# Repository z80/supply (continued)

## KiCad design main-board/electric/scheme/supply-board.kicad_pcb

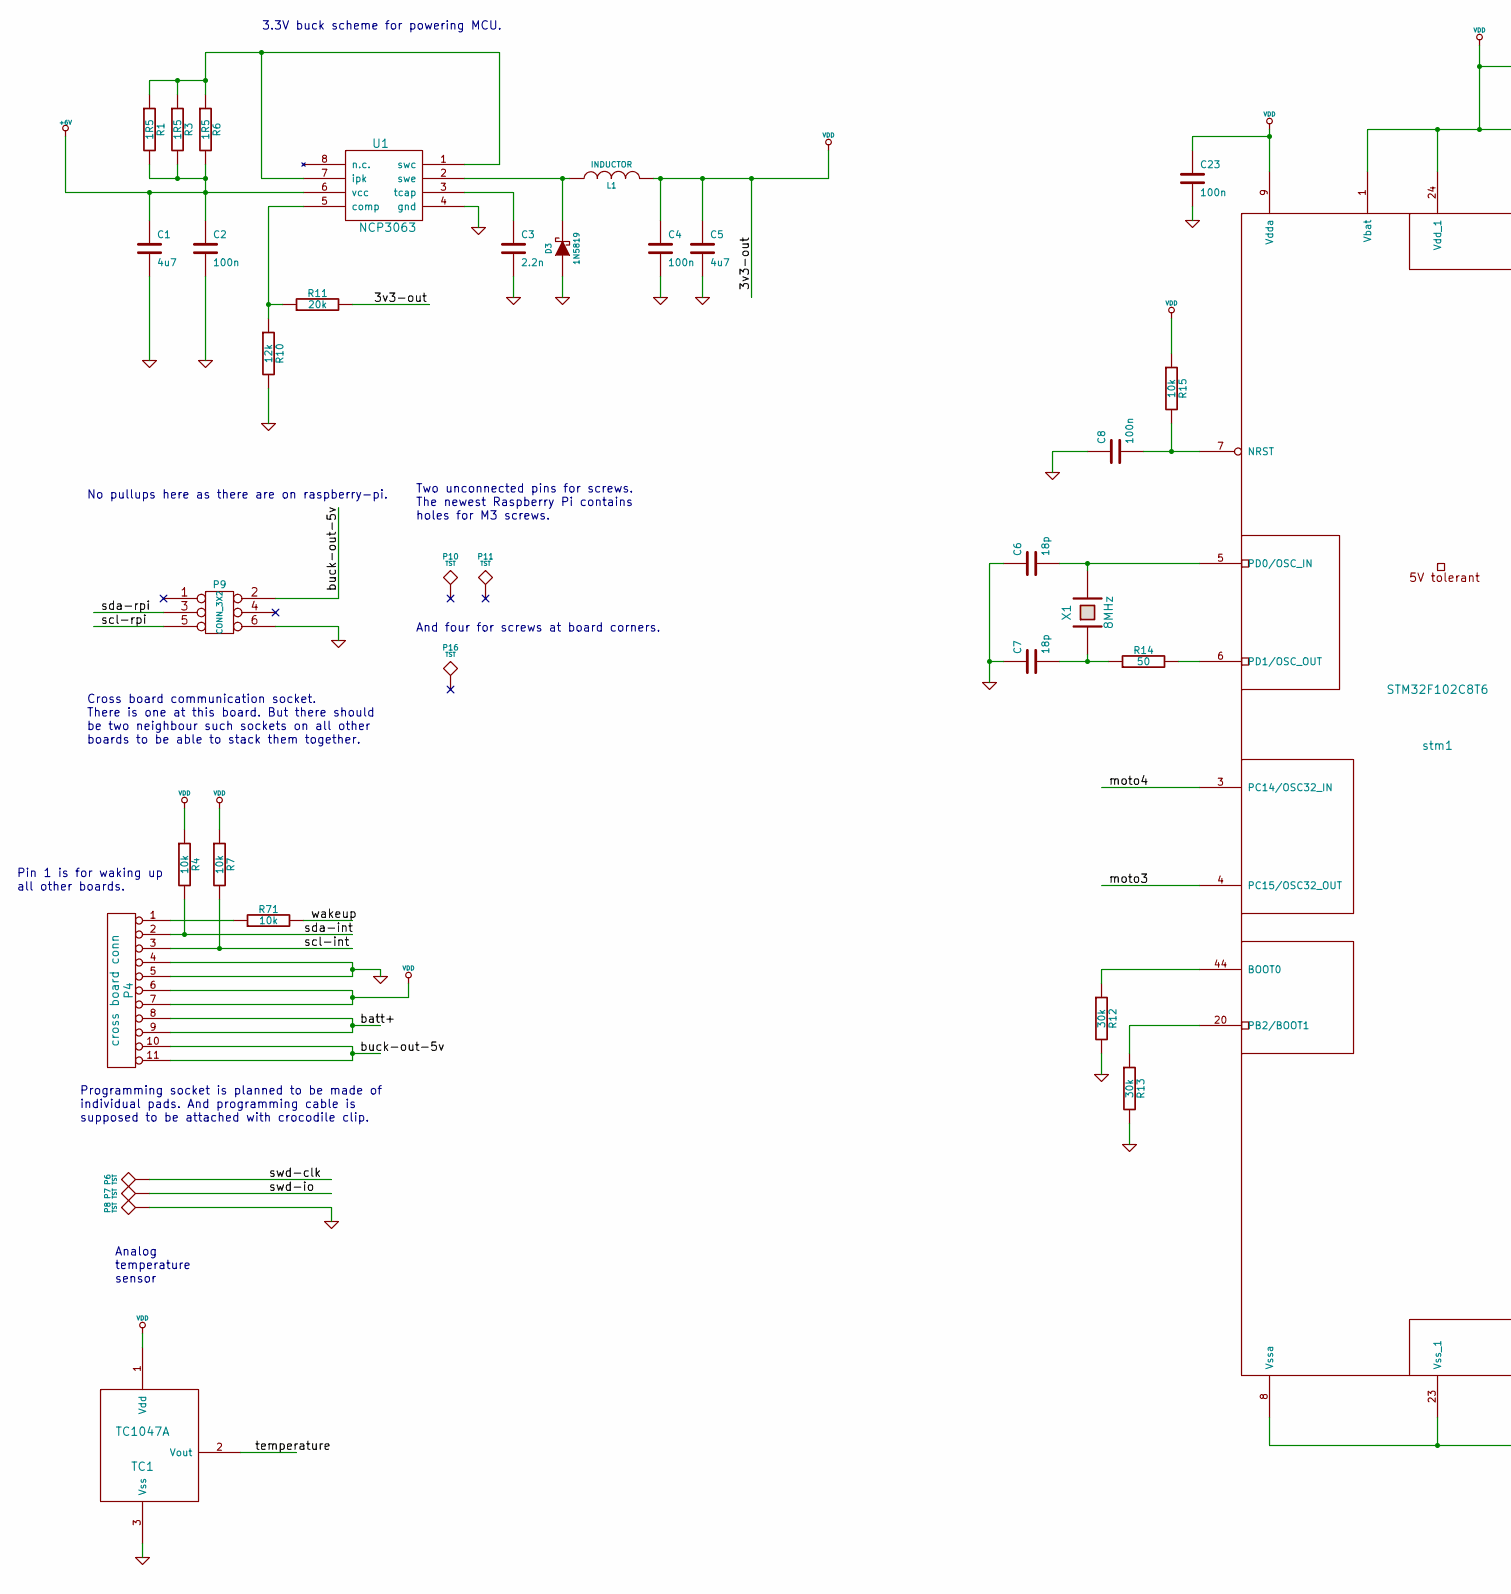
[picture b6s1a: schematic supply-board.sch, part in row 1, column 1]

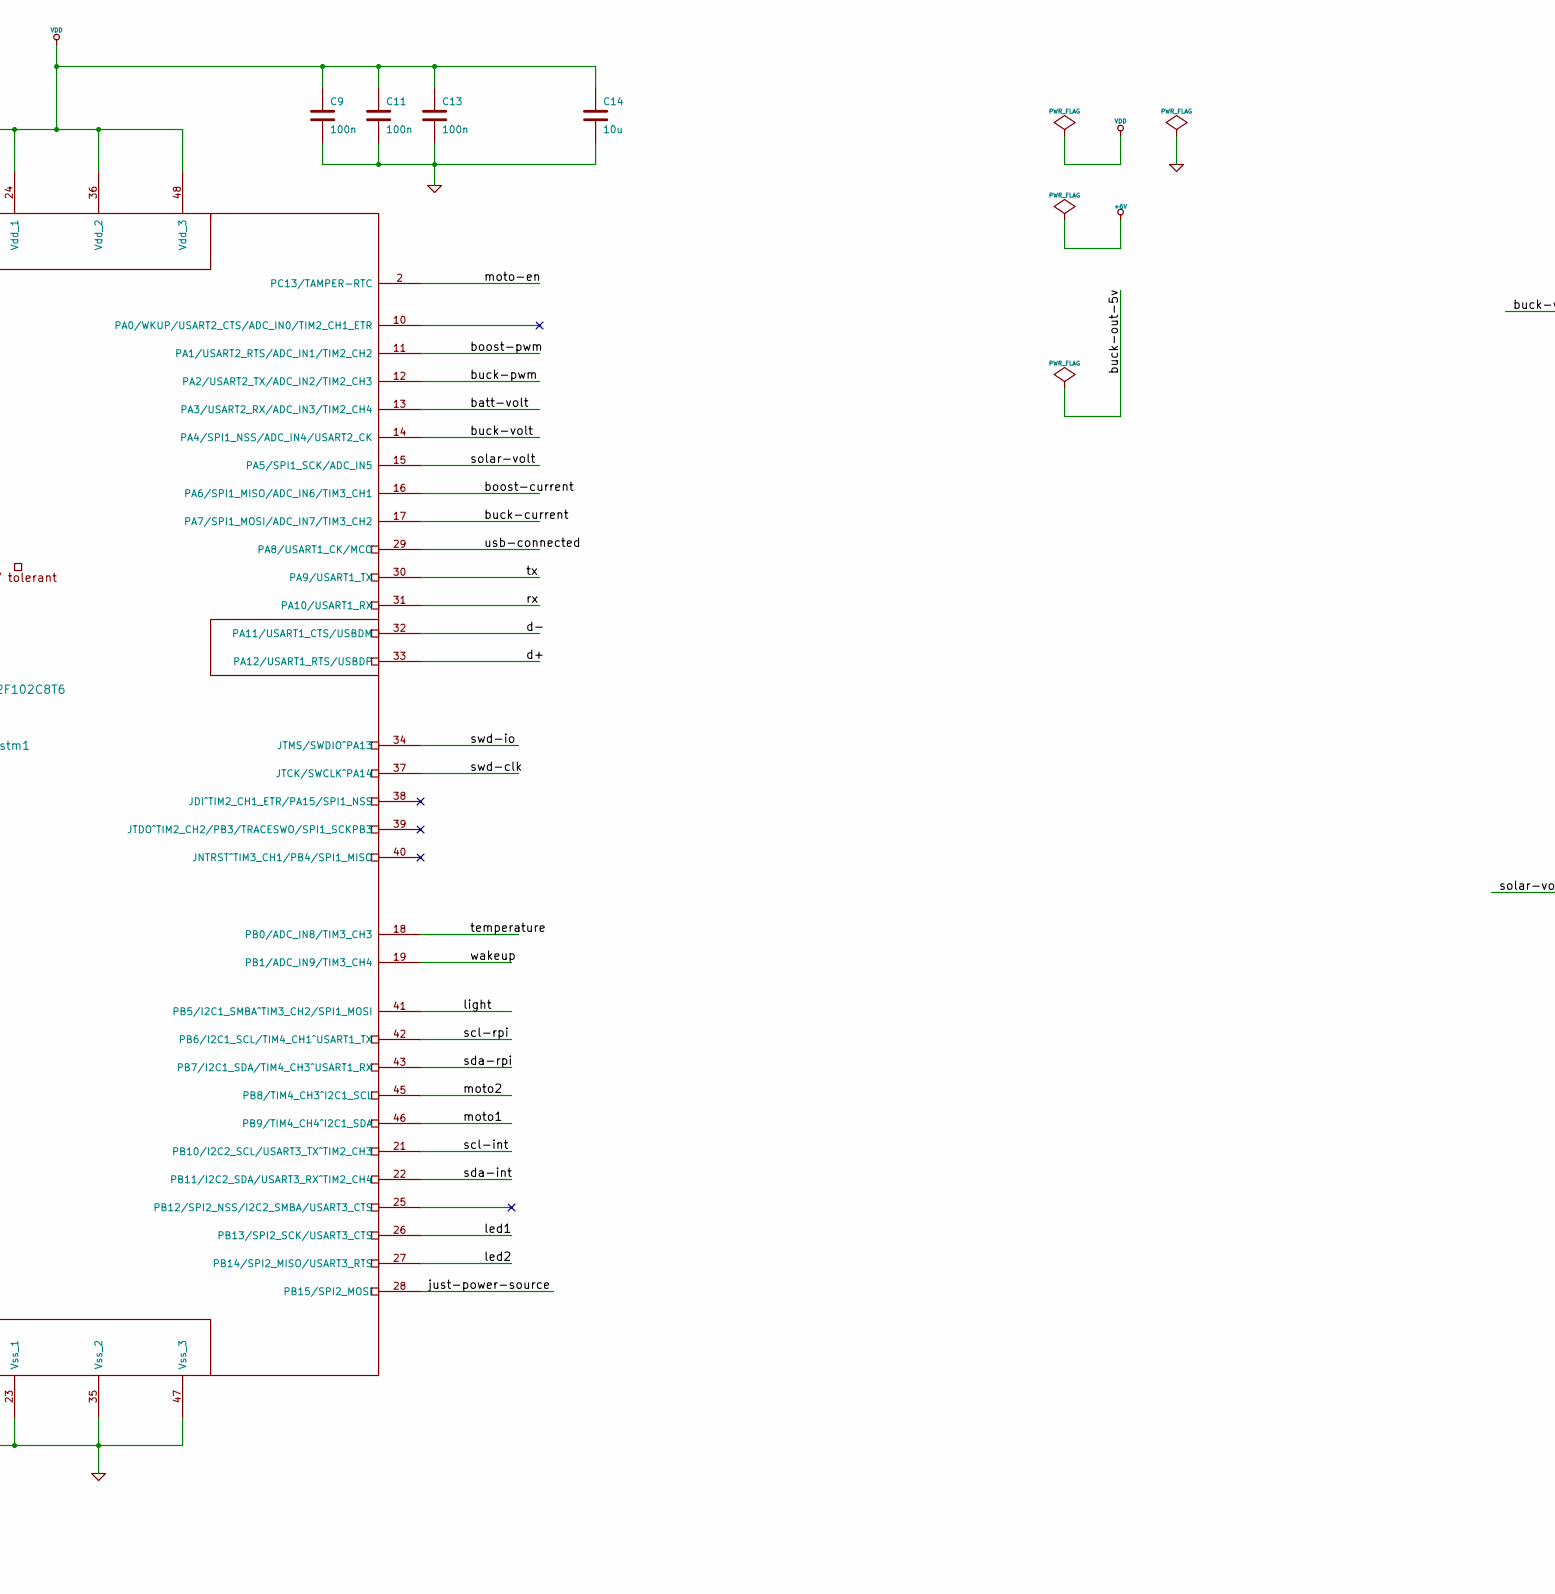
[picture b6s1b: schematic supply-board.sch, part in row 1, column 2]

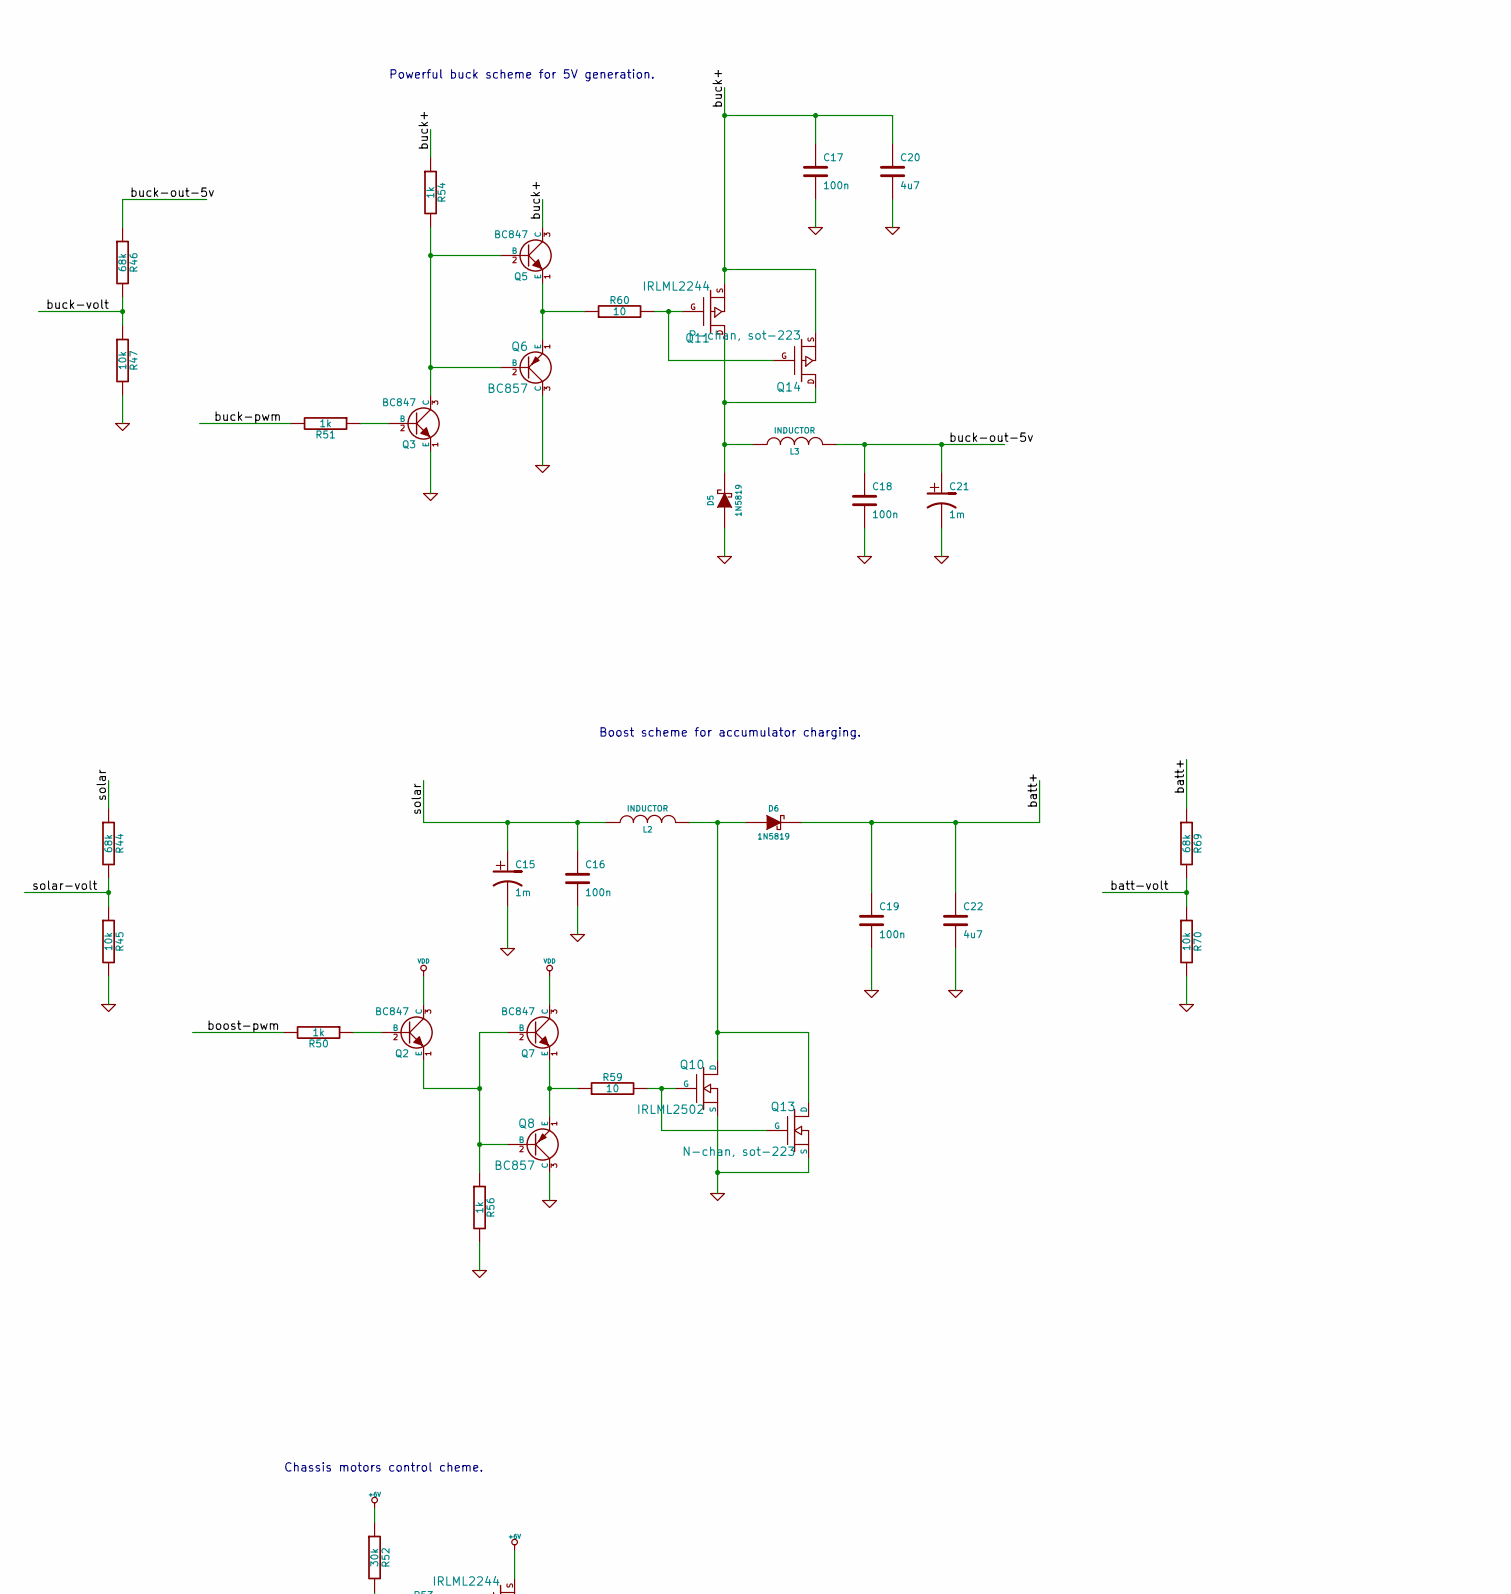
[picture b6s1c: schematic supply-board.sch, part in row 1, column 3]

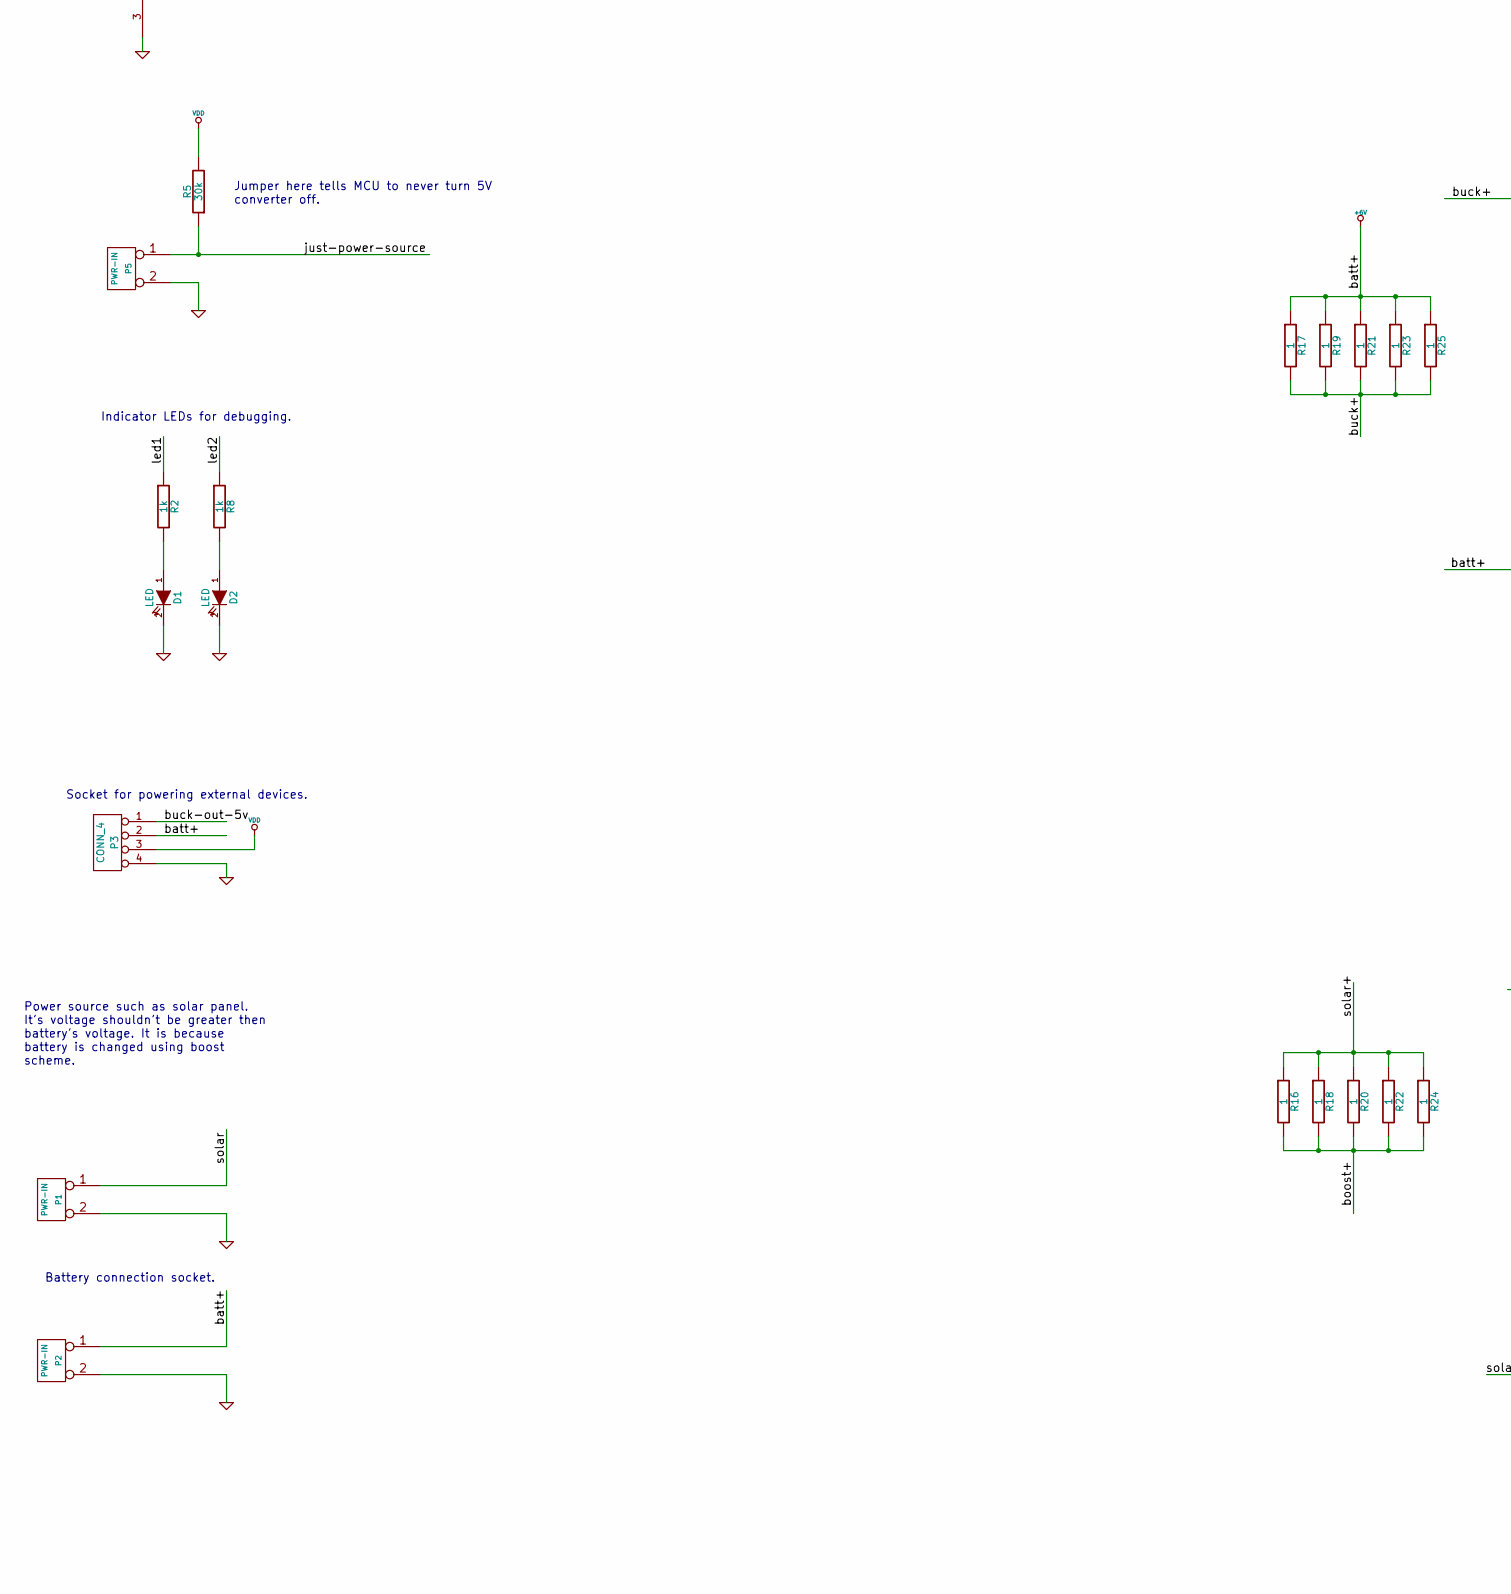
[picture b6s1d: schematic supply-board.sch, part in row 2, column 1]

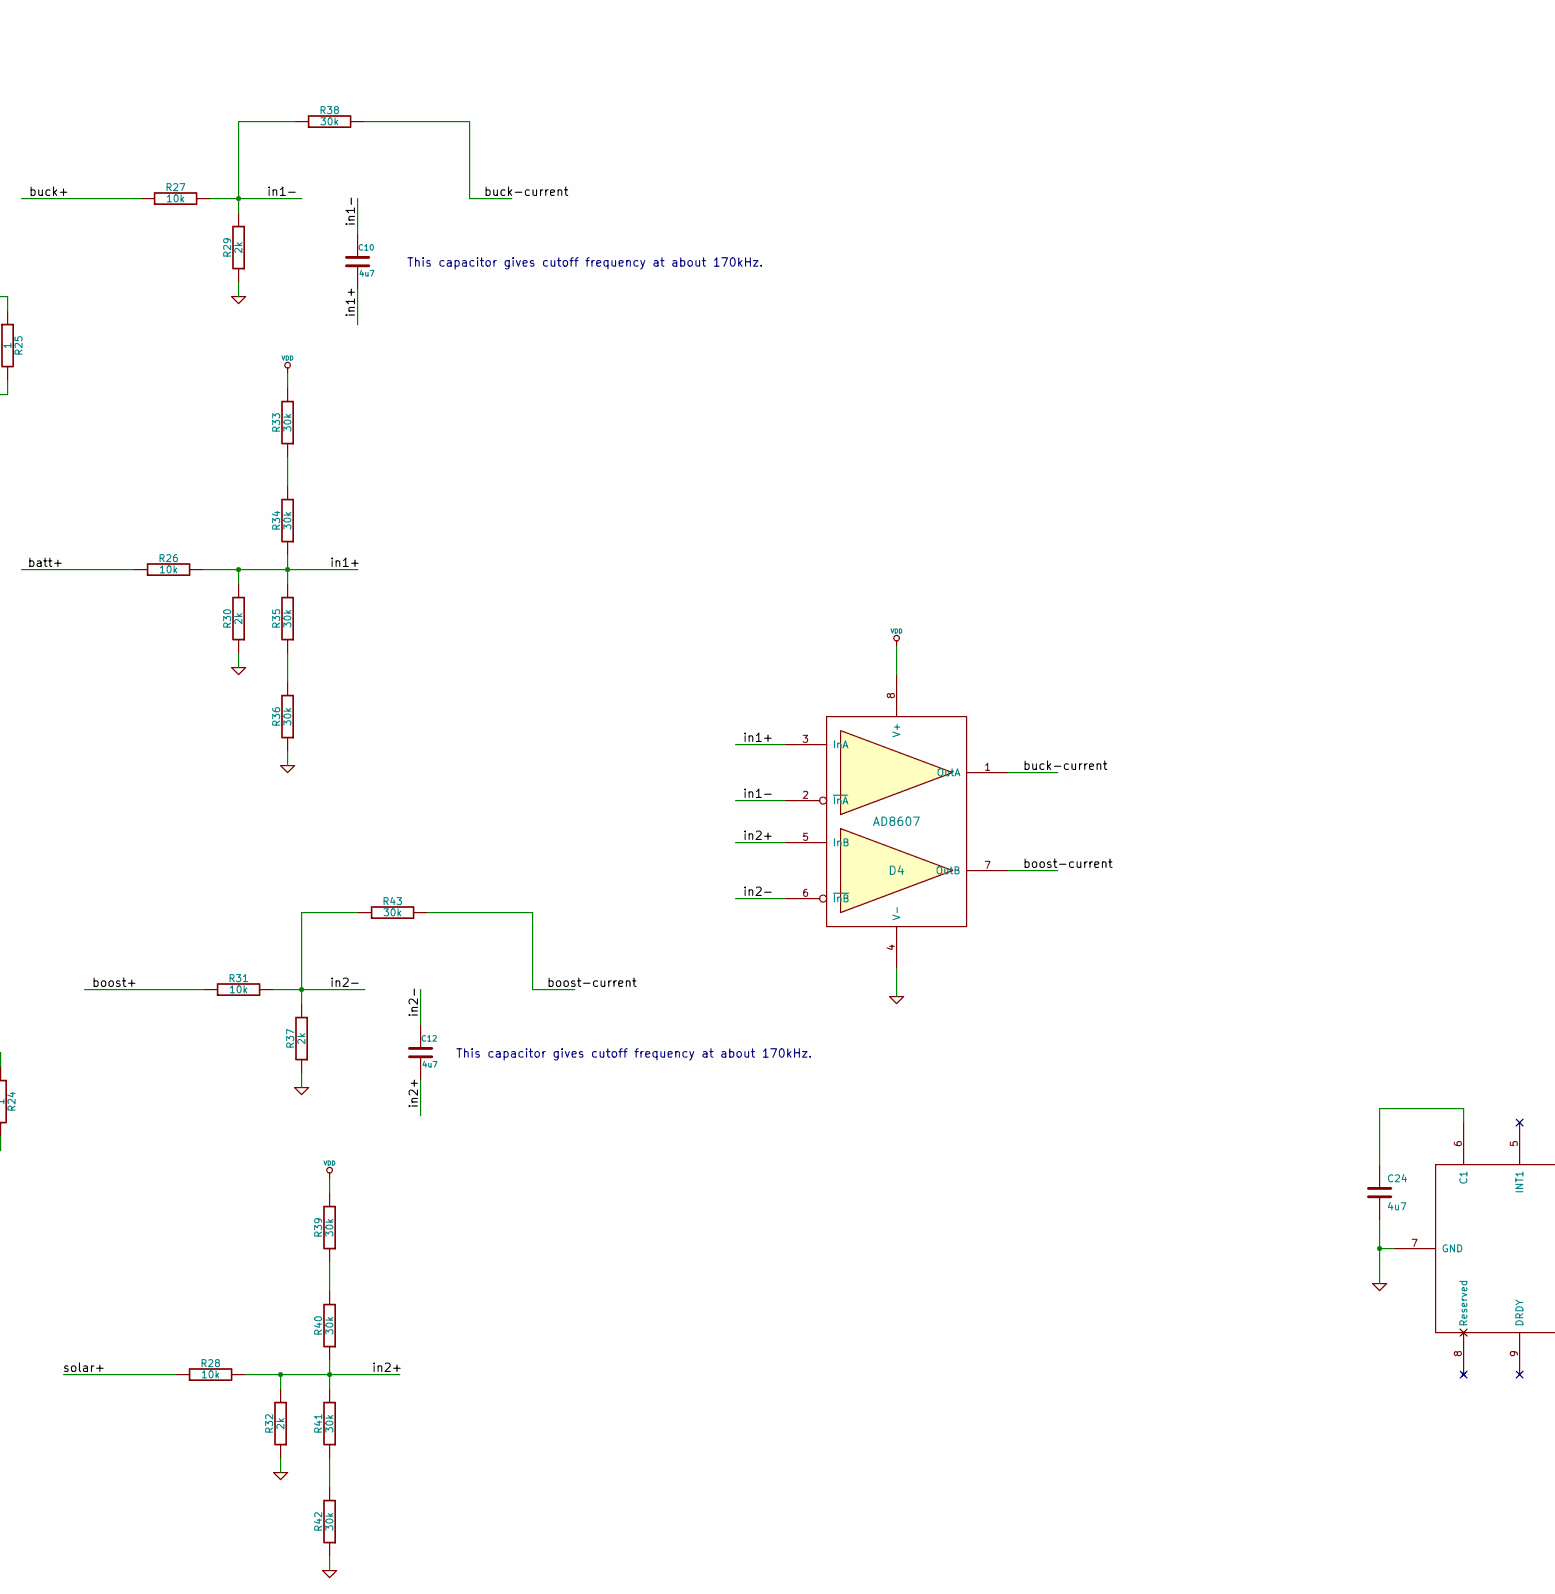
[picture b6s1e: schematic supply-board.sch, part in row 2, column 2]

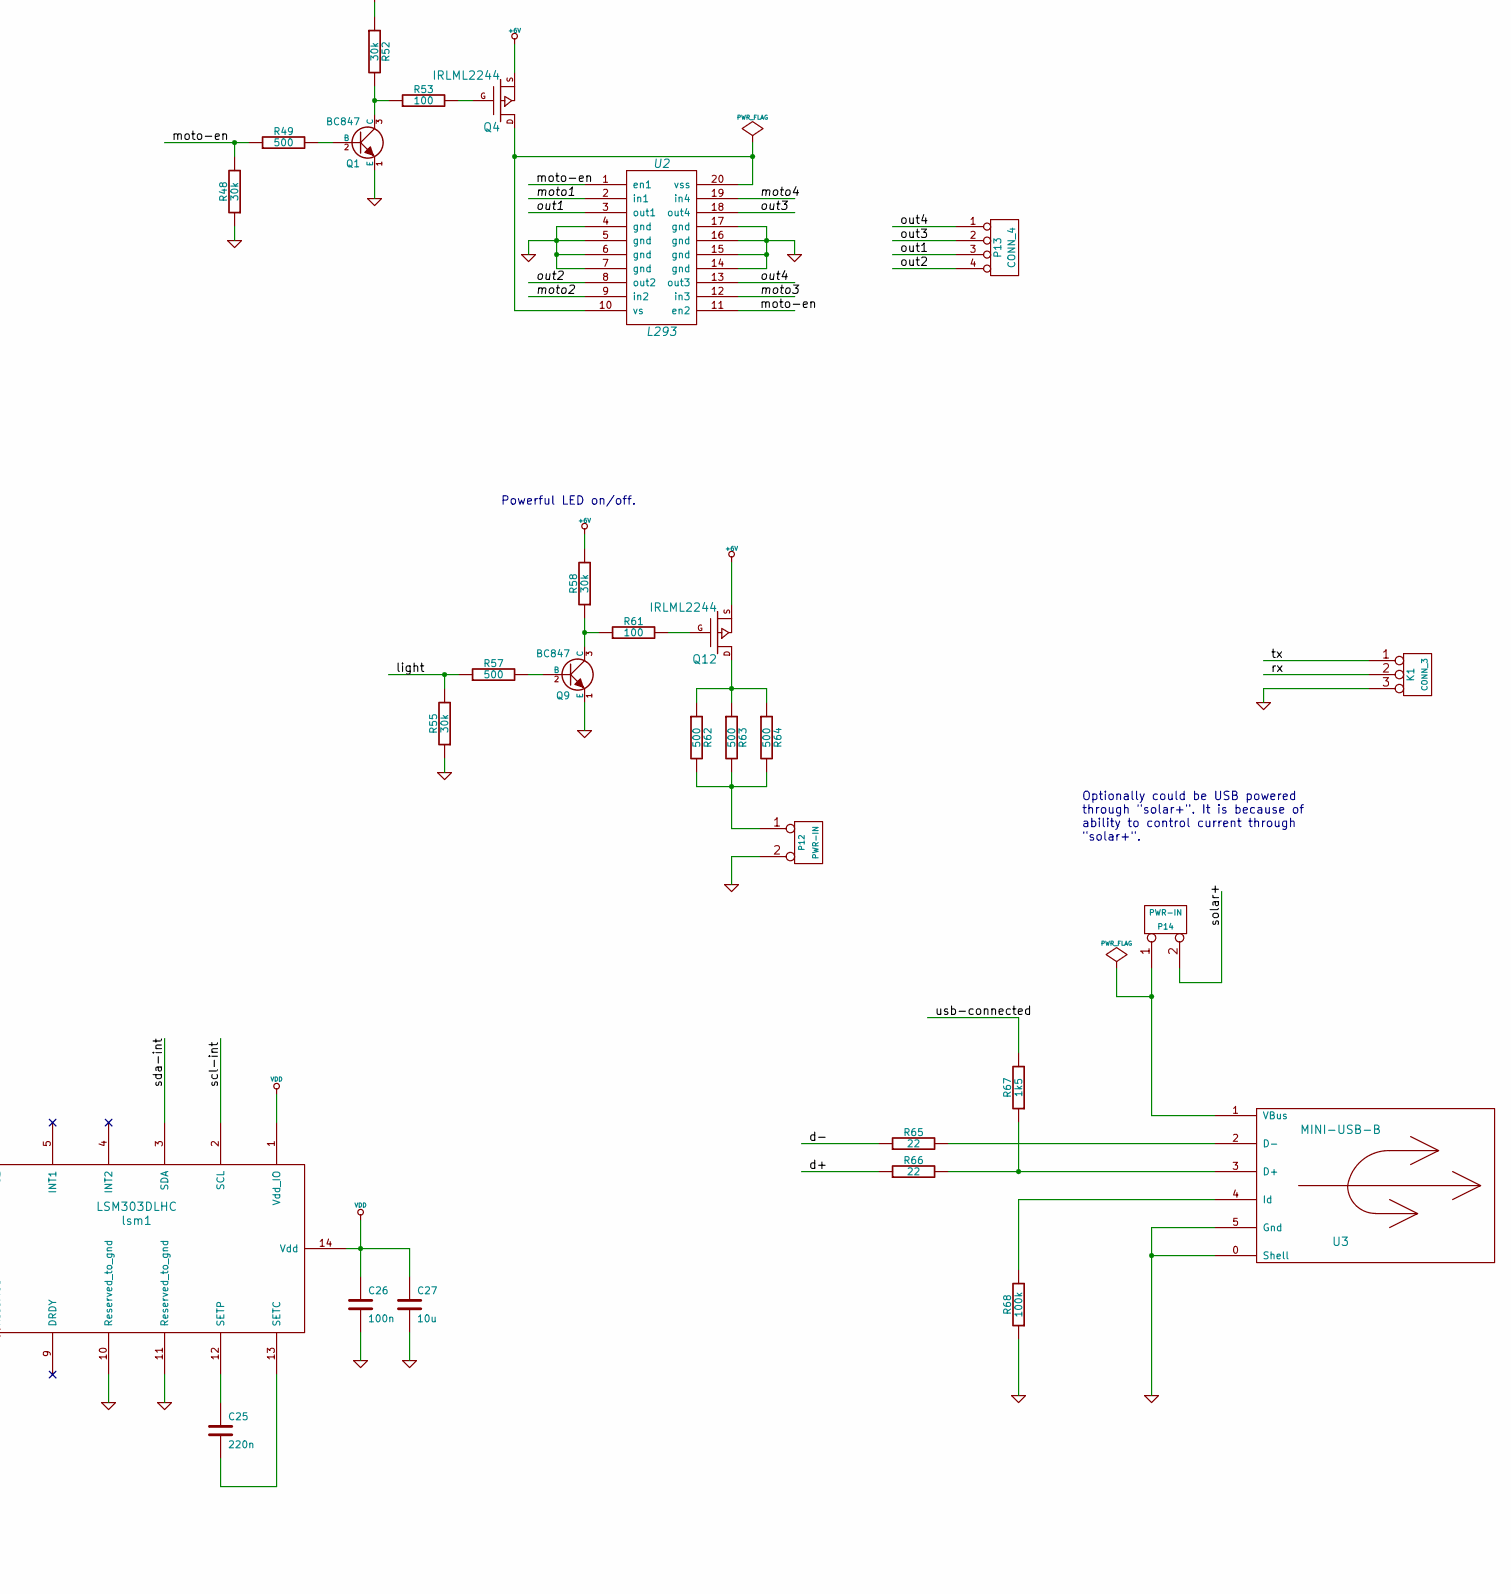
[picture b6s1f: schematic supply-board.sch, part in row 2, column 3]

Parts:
C1, C5, C20, C22, C24: 4u7
C2, C4, C8, C9, C11, C13, C16, C17, C18, C19, C23, C26: 100n
C3: 2.2n
C6, C7: 18p
C10, C12: 4u7
C14, C27: 10u
C15, C21: 1m
C25: 220n
D1, D2: LED
D3, D5, D6: 1N5819
D4: AD8607
K1: CONN_3
L1, L2, L3: INDUCTOR
P1, P2, P5, P12, P14: PWR-IN
P3, P13: CONN_4
P4: cross board conn
P6, P7, P8, P10, P11, P16: TST
P9: CONN_3X2
Q1, Q2, Q3, Q5, Q7, Q9: BC847
Q4, Q11, Q12: IRLML2244
Q6, Q8: BC857
Q10: IRLML2502
Q13: N-chan, sot-223
Q14: P-chan, sot-223
R1, R3, R6: 1R5
R2, R8, R50, R51, R54, R56: 1k
R4, R7, R15, R26, R27, R28, R31, R45, R47, R70, R71: 10k
R5, R12, R13, R33, R34, R35, R36, R38, R39, R40, R41, R42, R43, R48, R52, R55, R58: 30k
R10: 12k
R11: 20k
R14: 50
R16, R17, R18, R19, R20, R21, R22, R23, R24, R25: 1
R29, R30, R32, R37: 2k
R44, R46, R69: 68k
R49, R57, R62, R63, R64: 500
R53, R61: 100
R59, R60: 10
R65, R66: 22
R67: 1k5
R68: 100k
TC1: TC1047A
U1: NCP3063
U2: L293
U3: MINI-USB-B
X1: 8MHz
lsm1: LSM303DLHC
stm1: STM32F102C8T6

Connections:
+6V: C1.1, C2.1, C19.1, C22.1, D6.2 (K), P2.1, P3.2, P4.8, P4.9, Q4.S, Q12.S, R1.2, R3.2, R6.2, R17.1, R19.1, R21.1, R23.1, R25.1, R26.1, R52.1, R58.2, R69.1, U1.6 (vcc)
/batt-volt: R69.2, R70.1, stm1.13 (PA3/USART2_RX/ADC_IN3/TIM2_CH4)
/boost+: R16.2, R18.2, R20.2, R22.2, R24.2, R31.1
/boost-current: D4.7 (OutB), R43.2, stm1.16 (PA6/SPI1_MISO/ADC_IN6/TIM3_CH1)
/boost-pwm: R50.2, stm1.11 (PA1/USART2_RTS/ADC_IN1/TIM2_CH2)
/buck+: C17.1, C20.1, Q5.3 (C), Q11.S, Q14.S, R17.2, R19.2, R21.2, R23.2, R25.2, R27.1, R54.1
/buck-current: D4.1 (OutA), R38.2, stm1.17 (PA7/SPI1_MOSI/ADC_IN7/TIM3_CH2)
/buck-out-5v: C18.1, C21.1, L3.2, P3.1, P4.10, P4.11, P9.2, R46.1
/buck-pwm: R51.2, stm1.12 (PA2/USART2_TX/ADC_IN2/TIM2_CH3)
/buck-volt: R46.2, R47.1, stm1.14 (PA4/SPI1_NSS/ADC_IN4/USART2_CK)
/d+: R66.1, stm1.33 (PA12/USART1_RTS/USBDP)
/d-: R65.1, stm1.32 (PA11/USART1_CTS/USBDM)
/in1+: C10.2, D4.3 (InA), R26.2, R30.2, R34.1, R35.2
/in1-: C10.1, D4.2 (~InA~), R27.2, R29.2, R38.1
/in2+: C12.2, D4.5 (InB), R28.2, R32.2, R40.1, R41.2
/in2-: C12.1, D4.6 (~InB~), R31.2, R37.2, R43.1
/just-power-source: P5.1, R5.1, stm1.28 (PB15/SPI2_MOSI)
/led1: R2.1, stm1.26 (PB13/SPI2_SCK/USART3_CTS)
/led2: R8.1, stm1.27 (PB14/SPI2_MISO/USART3_RTS)
/light: R55.2, R57.1, stm1.41 (PB5/I2C1_SMBA^TIM3_CH2/SPI1_MOSI)
/moto1: U2.2 (in1), stm1.46 (PB9/TIM4_CH4^I2C1_SDA)
/moto2: U2.9 (in2), stm1.45 (PB8/TIM4_CH3^I2C1_SCL)
/moto3: U2.12 (in3), stm1.4 (PC15/OSC32_OUT)
/moto4: U2.19 (in4), stm1.3 (PC14/OSC32_IN)
/moto-en: R48.2, R49.1, U2.1 (en1), U2.11 (en2), stm1.2 (PC13/TAMPER-RTC)
/out1: P13.3, U2.3 (out1)
/out2: P13.4, U2.8 (out2)
/out3: P13.2, U2.18 (out4)
/out4: P13.1, U2.13 (out3)
/rx: K1.2 (PM), stm1.31 (PA10/USART1_RX)
/scl-int: P4.3, R7.2, lsm1.2 (SCL), stm1.21 (PB10/I2C2_SCL/USART3_TX^TIM2_CH3)
/scl-rpi: P9.5, stm1.42 (PB6/I2C1_SCL/TIM4_CH1^USART1_TX)
/sda-int: P4.2, R4.2, lsm1.3 (SDA), stm1.22 (PB11/I2C2_SDA/USART3_RX^TIM2_CH4)
/sda-rpi: P9.3, stm1.43 (PB7/I2C1_SDA/TIM4_CH3^USART1_RX)
/solar: C15.1, C16.1, L2.1, P1.1, R44.1
/solar+: P14.2 (PM), R16.1, R18.1, R20.1, R22.1, R24.1, R28.1
/solar-volt: R44.2, R45.1, stm1.15 (PA5/SPI1_SCK/ADC_IN5)
/swd-clk: P6.1, stm1.37 (JTCK/SWCLK^PA14)
/swd-io: P7.1, stm1.34 (JTMS/SWDIO^PA13)
/temperature: TC1.2 (Vout), stm1.18 (PB0/ADC_IN8/TIM3_CH3)
/tx: K1.1, stm1.30 (PA9/USART1_TX)
/usb-connected: R67.2, stm1.29 (PA8/USART1_CK/MCO)
/wakeup: R71.2, stm1.19 (PB1/ADC_IN9/TIM3_CH4)
GND: C1.2, C2.2, C3.2, C4.2, C5.2, C6.1, C7.1, C8.1, C9.2, C11.2, C13.2, C14.2, C15.2, C16.2, C17.2, C18.2, C19.2, C20.2, C21.2, C22.2, C23.2, C24.2, C26.2, C27.2, D1.2 (K), D2.2 (K), D3.1 (A), D4.4 (V-), D5.1 (A), K1.3, P1.2 (PM), P2.2 (PM), P3.4, P4.4, P4.5, P5.2 (PM), P8.1, P9.6, P12.2 (PM), Q1.1 (E), Q3.1 (E), Q6.3 (C), Q8.3 (C), Q9.1 (E), Q10.S, Q13.S, R10.2, R12.2, R13.2, R29.1, R30.1, R32.1, R36.1, R37.1, R42.1, R45.2, R47.2, R48.1, R55.1, R56.2, R68.1, R70.2, TC1.3 (Vss), U1.4 (gnd), U2.4 (gnd), U2.5 (gnd), U2.6 (gnd), U2.7 (gnd), U2.14 (gnd), U2.15 (gnd), U2.16 (gnd), U2.17 (gnd), U3.0 (Shell), U3.5 (Gnd), lsm1.7 (GND), lsm1.10 (Reserved_to_gnd), lsm1.11 (Reserved_to_gnd), stm1.8 (Vssa), stm1.23 (Vss_1), stm1.35 (Vss_2), stm1.47 (Vss_3)
unnamed: Q4.D, U2.10 (vs), U2.20 (vss)
unnamed: Q12.G, R61.2
unnamed: Q1.2 (B), R49.2
unnamed: Q4.G, R53.2
unnamed: Q5.1 (E), Q6.1 (E), R60.1
unnamed: Q3.3 (C), Q5.2 (B), Q6.2 (B), R54.2
unnamed: D5.2 (K), L3.1, Q11.D, Q14.D
unnamed: Q2.1 (E), Q7.2 (B), Q8.2 (B), R56.1
unnamed: Q2.2 (B), R50.1
unnamed: R35.1, R36.2
unnamed: R33.1, R34.2
unnamed: R65.2, U3.2 (D-)
unnamed: R68.2, U3.4 (Id)
unnamed: R66.2, R67.1, U3.3 (D+)
unnamed: R10.1, R11.1, U1.5 (comp)
unnamed: R1.1, R3.1, R6.1, U1.1 (swc), U1.7 (ipk)
unnamed: C3.1, U1.3 (tcap)
unnamed: C8.2, R15.2, stm1.7 (NRST)
unnamed: R12.1, stm1.44 (BOOT0)
unnamed: C6.2, X1.2, stm1.5 (PD0/OSC_IN)
unnamed: R14.2, stm1.6 (PD1/OSC_OUT)
unnamed: R13.1, stm1.20 (PB2/BOOT1)
unnamed: C7.2, R14.1, X1.1
unnamed: Q7.1 (E), Q8.1 (E), R59.1
unnamed: Q3.2 (B), R51.1
unnamed: D2.1 (A), R8.2
unnamed: D1.1 (A), R2.2
unnamed: D3.2 (K), L1.1, U1.2 (swe)
unnamed: P4.1, R71.1
unnamed: C25.1, lsm1.12 (SETP)
unnamed: P14.1, U3.1 (VBus)
unnamed: Q11.G, Q14.G, R60.2
unnamed: Q10.G, Q13.G, R59.2
unnamed: D6.1 (A), L2.2, Q10.D, Q13.D
unnamed: C24.1, lsm1.6 (C1)
unnamed: C25.2, lsm1.13 (SETC)
unnamed: R41.1, R42.2
unnamed: R39.1, R40.2
unnamed: Q1.3 (C), R52.2, R53.1
unnamed: P12.1, R62.2, R63.2, R64.2
unnamed: Q9.3 (C), R58.1, R61.1
unnamed: Q9.2 (B), R57.2
unnamed: Q12.D, R62.1, R63.1, R64.1
VDD: C4.1, C5.1, C9.1, C11.1, C13.1, C14.1, C23.1, C26.1, C27.1, D4.8 (V+), L1.2, P3.3, P4.6, P4.7, Q2.3 (C), Q7.3 (C), R4.1, R5.2, R7.1, R11.2, R15.1, R33.2, R39.2, TC1.1 (Vdd), lsm1.1 (Vdd_IO), lsm1.14 (Vdd), stm1.1 (Vbat), stm1.9 (Vdda), stm1.24 (Vdd_1), stm1.36 (Vdd_2), stm1.48 (Vdd_3)

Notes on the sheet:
3.3V buck scheme for powering MCU.
Powerful buck scheme for 5V generation.
Boost scheme for accumulator charging.
Chassis motors control cheme.
Indicator LEDs for debugging.
Powerful LED on/off.
Jumper here tells MCU to never turn 5V converter off.
Analog temperature sensor
No pullups here as there are on raspberry-pi.
Power source such as solar panel. It's voltage shouldn't be greater then battery's voltage. It is because battery is changed using boost scheme.
Battery connection socket.
Programming socket is planned to be made of individual pads. And programming cable is supposed to be attached with crocodile clip.
Cross board communication socket. There is one at this board. But there should be two neighbour such sockets on all other boards to be able to stack them together.
Two unconnected pins for screws. The newest Raspberry Pi contains holes for M3 screws.
Socket for powering external devices.
Optionally could be USB powered through "solar+". It is because of ability to control current through "solar+".
This capacitor gives cutoff frequency at about 170kHz.
And four for screws at board corners.
Pin 1 is for waking up all other boards.

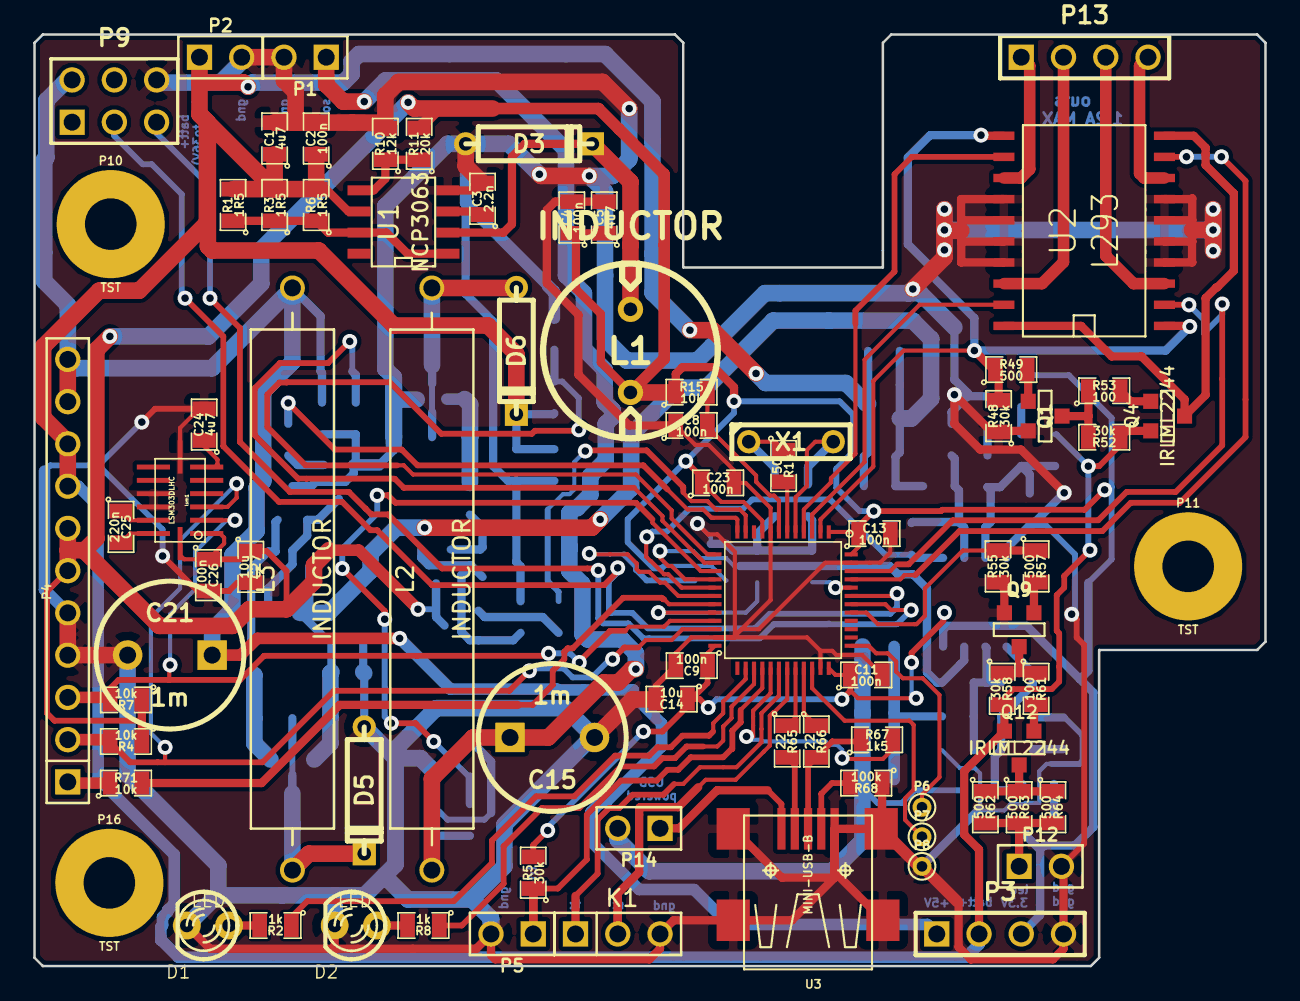
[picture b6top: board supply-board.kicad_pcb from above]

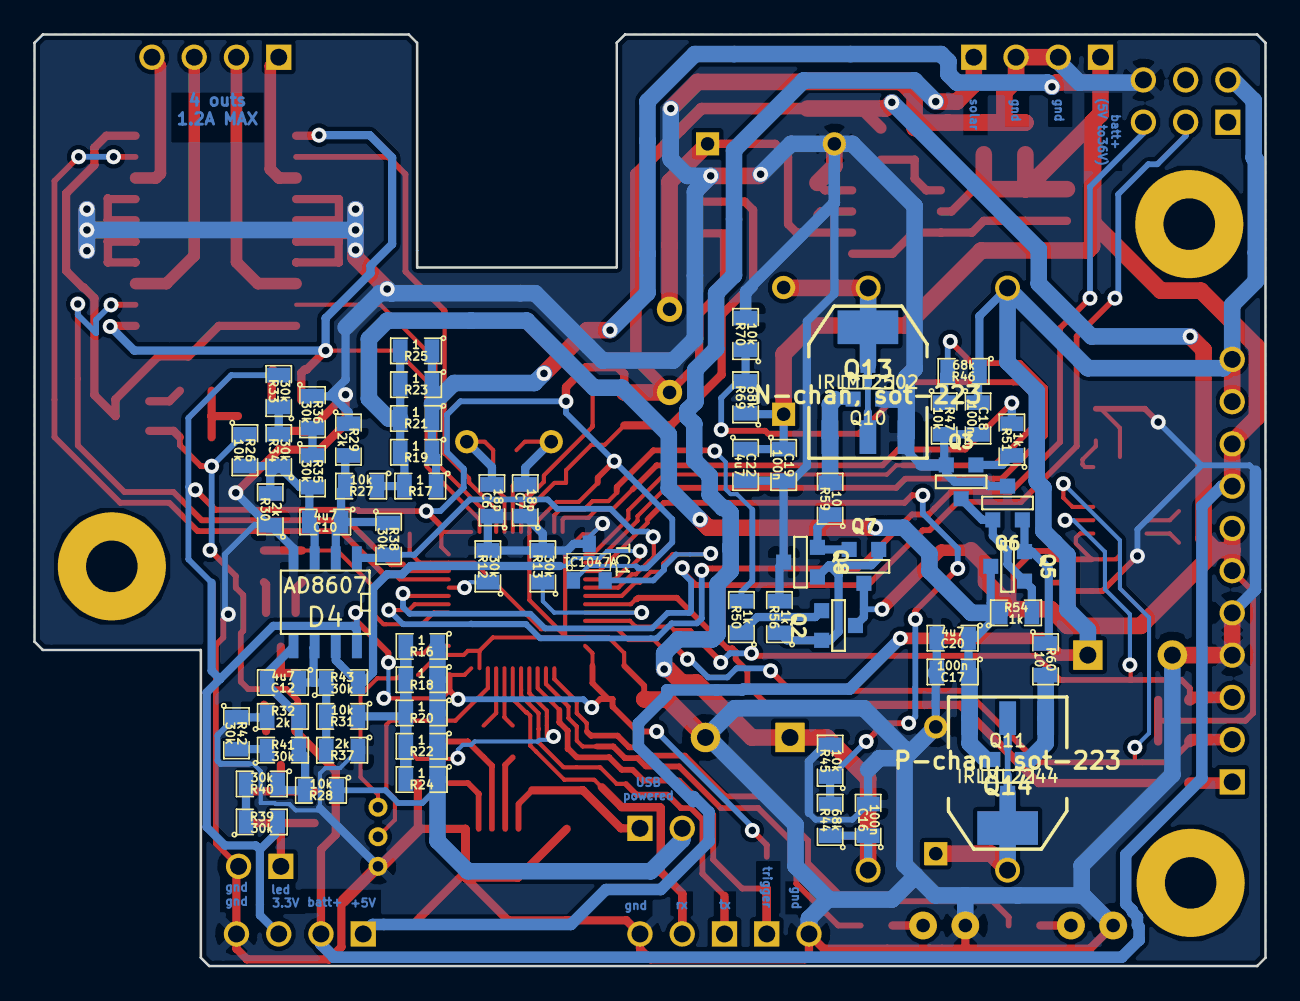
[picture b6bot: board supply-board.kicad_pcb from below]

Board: 2 copper layers, 74.0 x 56.0 mm, 143 parts (64 on the bottom side), 88 nets.
